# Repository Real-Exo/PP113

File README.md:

Portable version of the Project 113 headphone amplifier, with added BlueTooth and 3D printable case.
Powered by 4 removable 18650 Li-ion cells, have to be charged externally.
Kicad 7.0 schematics & PCB layouts.
MPLAB X IDE firmware project.
FreeCAD case design files & gcode.

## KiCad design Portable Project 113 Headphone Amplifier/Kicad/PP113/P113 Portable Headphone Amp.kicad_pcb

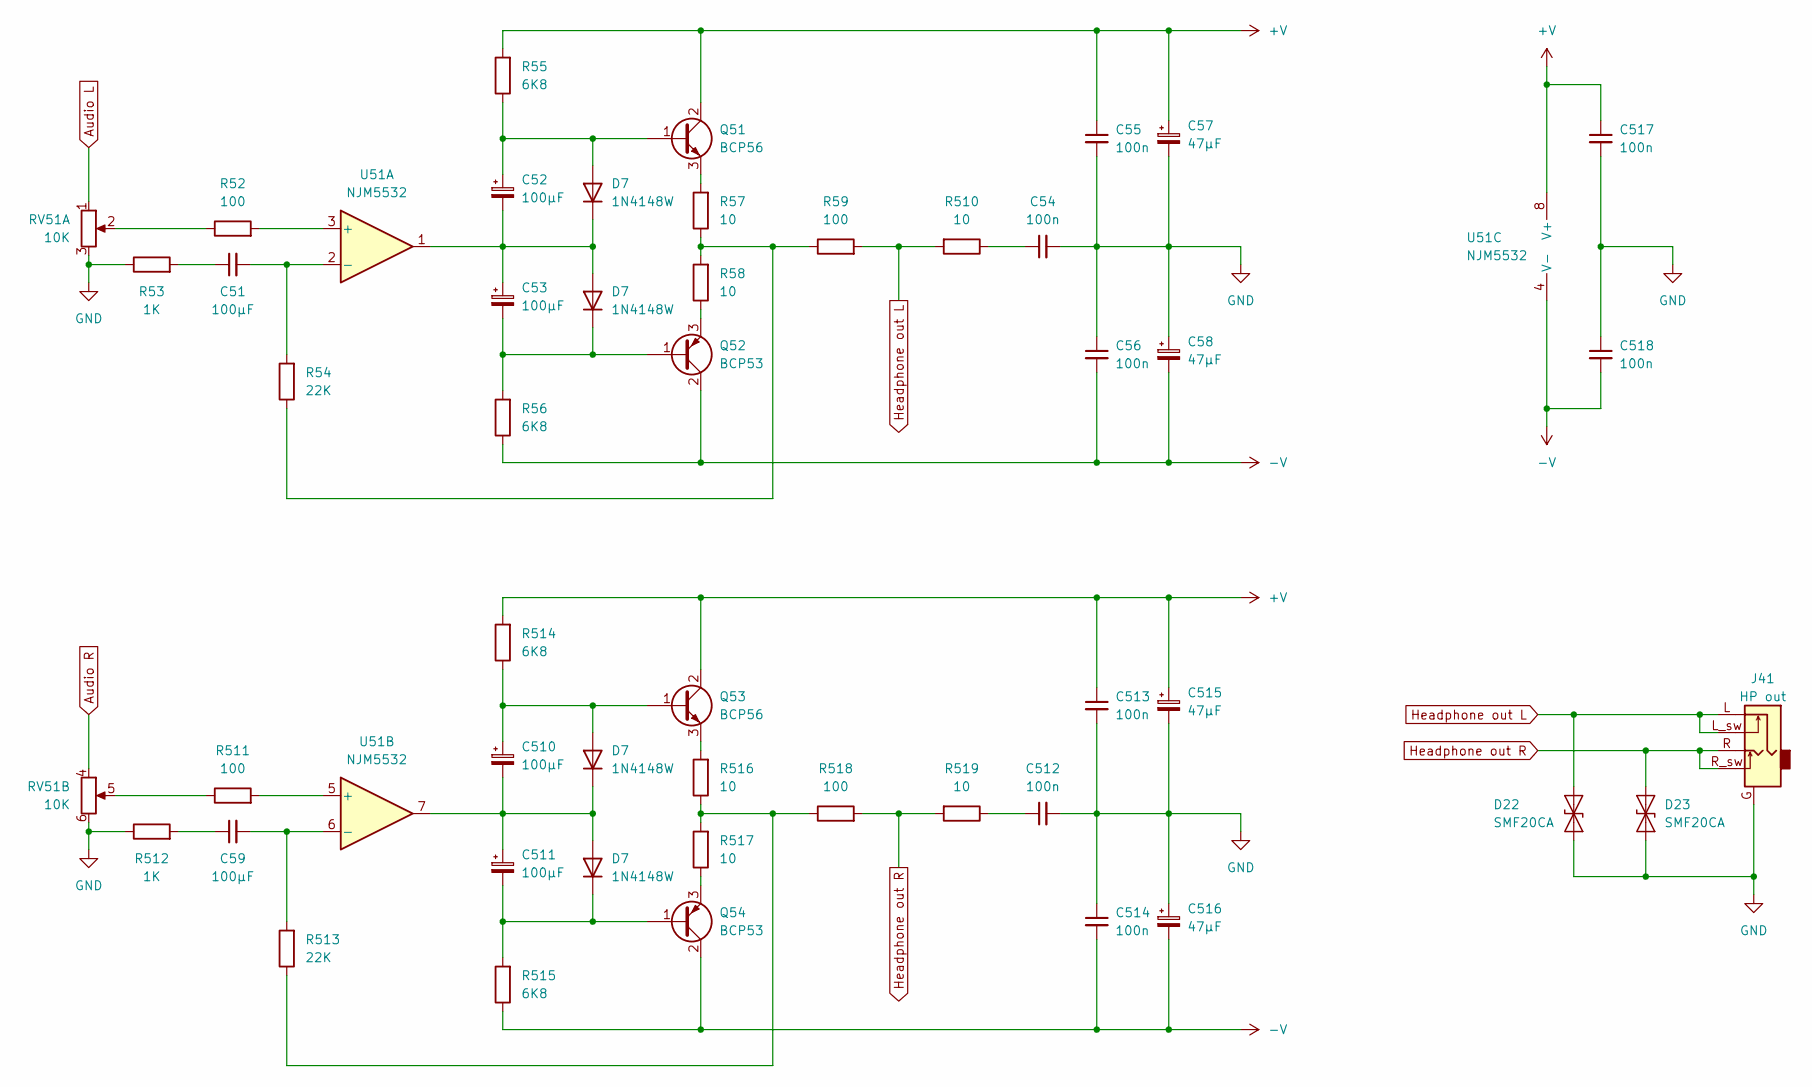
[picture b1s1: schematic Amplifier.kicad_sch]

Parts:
C51, C59: 100µF; CP_Elec_8x5.4
C52, C53, C510, C511: 100µF; CP_Elec_6.3x5.4_Nichicon
C54, C55, C56, C512, C513, C514, C517, C518: 100n; C_0805_2012Metric_Pad1.18x1.45mm_HandSolder
C57, C58, C515, C516: 47µF; CP_Elec_6.3x5.7
D7: 1N4148W; D_SOD-123
D22, D23: SMF20CA; D_SOD-123
J41: HP out; 3-5mm_connector
Q51, Q53: BCP56; SOT-223-3_TabPin2
Q52, Q54: BCP53; SOT-223-3_TabPin2
R52, R511: 100; R_0805_2012Metric_Pad1.20x1.40mm_HandSolder
R53, R512: 1K; R_0805_2012Metric_Pad1.20x1.40mm_HandSolder
R54, R513: 22K; R_0805_2012Metric_Pad1.20x1.40mm_HandSolder
R55, R56, R514, R515: 6K8; R_0805_2012Metric_Pad1.20x1.40mm_HandSolder
R57, R58, R510, R516, R517, R519: 10; R_1206_3216Metric_Pad1.30x1.75mm_HandSolder
R59, R518: 100; R_2512_6332Metric_Pad1.40x3.35mm_HandSolder
RV51: 10K; Potentiometer_Alps_RK09L_Double_Horizontal
U51: NJM5532; SOIC-8W_5.3x5.3mm_P1.27mm

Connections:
+V: C55.1, C57.1, C513.1, C515.1, C517.1, Q51.2 (C), Q53.2 (C), R55.2, R514.2, U51.8 (V+); also elsewhere on the board
-V: C56.2, C58.2, C514.2, C516.2, C518.2, Q52.2 (C), Q54.2 (C), R56.1, R515.1, U51.4 (V-); also elsewhere on the board
Audio L: RV51.1; also elsewhere on the board
Audio R: RV51.4; also elsewhere on the board
unnamed: C51.1, R53.2
unnamed: C54.1, R510.1
unnamed: C59.1, R512.2
unnamed: C512.1, R519.1
unnamed 55: C52.1, Q51.1 (B), R55.1; also elsewhere on the board
unnamed 56: C52.2, C53.1, U51.1; also elsewhere on the board
unnamed 57: C53.2, Q52.1 (B), R56.2; also elsewhere on the board
unnamed 58: C510.1, Q53.1 (B), R514.1; also elsewhere on the board
unnamed 59: C510.2, C511.1, U51.7; also elsewhere on the board
unnamed 60: C511.2, Q54.1 (B), R515.2; also elsewhere on the board
unnamed: Q51.3 (E), R57.2
unnamed: Q52.3 (E), R58.1
unnamed: Q53.3 (E), R516.2
unnamed: Q54.3 (E), R517.1
unnamed: R52.1, RV51.2
unnamed: R54.1, R57.1, R58.2, R59.1
unnamed: R511.1, RV51.5
unnamed: R513.1, R516.1, R517.2, R518.1
unnamed: R52.2, U51.3 (+)
unnamed: C51.2, R54.2, U51.2 (-)
unnamed: R511.2, U51.5 (+)
unnamed: C59.2, R513.2, U51.6 (-)

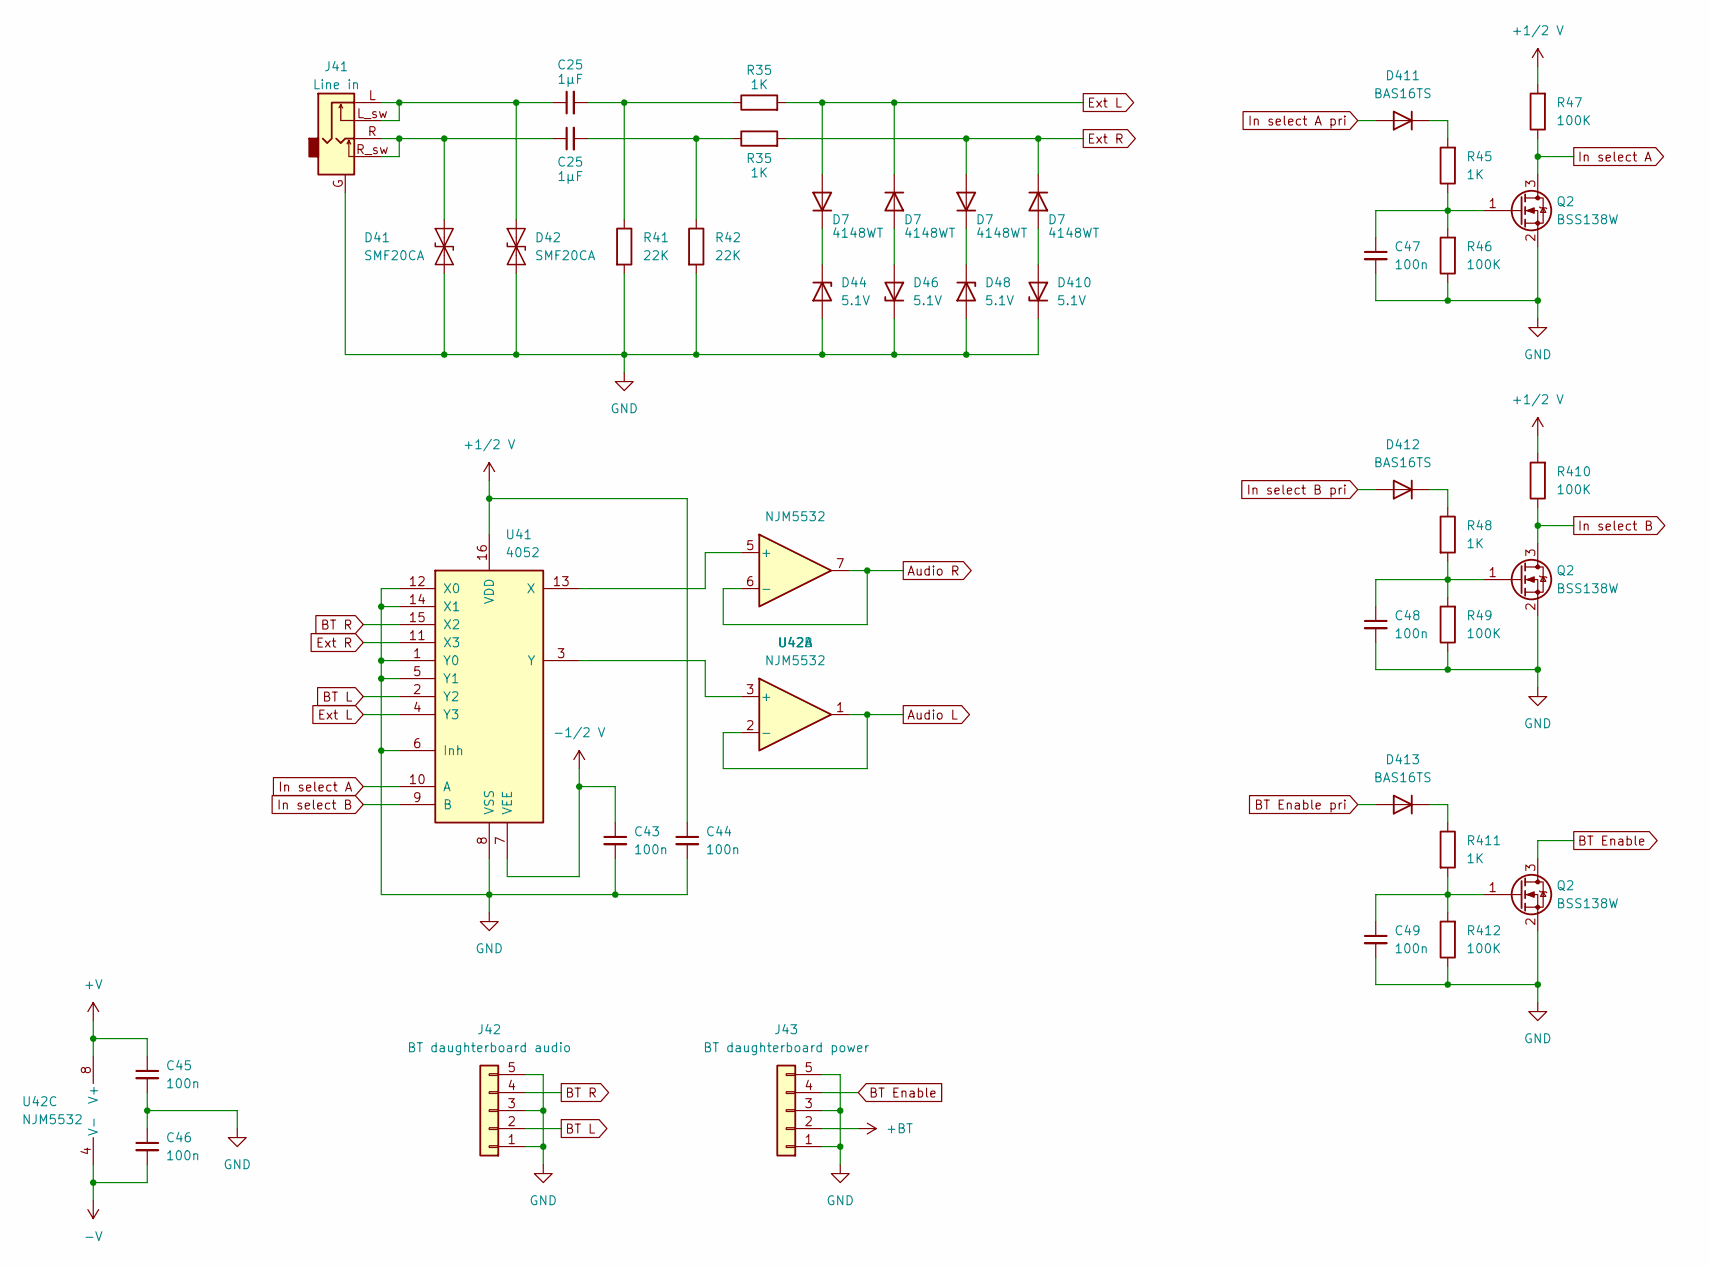
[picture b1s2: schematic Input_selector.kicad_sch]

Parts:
C25: 1µF; WIMA_1µF
C43, C44, C45, C46: 100n; C_0805_2012Metric_Pad1.18x1.45mm_HandSolder
C47, C48, C49: 100n; C_0402_1005Metric_Pad0.74x0.62mm_HandSolder JLC
D7: 4148WT; D_SOD-523
D41, D42: SMF20CA; D_SOD-123
D44, D46, D48, D410: 5.1V; D_SOD-323
D411, D412, D413: BAS16TS; D_SOD-523
J41: Line in; 3-5mm_connector
J42: BT daughterboard audio; PinSocket_1x05_P2.54mm_Vertical
J43: BT daughterboard power; PinSocket_1x05_P2.54mm_Vertical
Q2: BSS138W; SOT-323_SC-70
R35: 1K; R_2512_6332Metric_Pad1.40x3.35mm_HandSolder
R41, R42: 22K; R_1206_3216Metric_Pad1.30x1.75mm_HandSolder
R45, R48, R411: 1K; R_0402_1005Metric_Pad0.72x0.64mm_HandSolder JLC
R46, R47, R49, R410, R412: 100K; R_0402_1005Metric_Pad0.72x0.64mm_HandSolder JLC
U41: 4052; TSSOP-16_4.4x5mm_P0.65mm
U42: NJM5532; SOIC-8W_5.3x5.3mm_P1.27mm

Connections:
+1/2_V: C44.1, R47.2, R410.2, U41.16 (VDD); also elsewhere on the board
+BT: J43.2; also elsewhere on the board
+V: C45.1, U42.8 (V+); also elsewhere on the board
-1/2_V: C43.1, U41.7 (VEE); also elsewhere on the board
-V: C46.2, U42.4 (V-); also elsewhere on the board
Audio L: U42.1, U42.2 (-); also elsewhere on the board
Audio R: U42.6 (-), U42.7; also elsewhere on the board
BT Enable: J43.4; also elsewhere on the board
BT Enable pri: D413.2 (A); also elsewhere on the board
BT L: J42.2, U41.2 (Y2)
BT R: J42.4, U41.15 (X2)
Ext L: U41.4 (Y3); also elsewhere on the board
Ext R: U41.11 (X3); also elsewhere on the board
In select A: R47.1, U41.10 (A); also elsewhere on the board
In select A pri: D411.2 (A); also elsewhere on the board
In select B: R410.1, U41.9 (B); also elsewhere on the board
In select B pri: D412.2 (A); also elsewhere on the board
unnamed 52: D44.1 (K); also elsewhere on the board
unnamed 53: D46.2 (A); also elsewhere on the board
unnamed 54: D48.1 (K); also elsewhere on the board
unnamed 61: D410.2 (A); also elsewhere on the board
unnamed: D411.1 (K), R45.2
unnamed: D412.1 (K), R48.1
unnamed: D413.1 (K), R411.1
unnamed 92: C47.1, R45.1, R46.2; also elsewhere on the board
unnamed 93: C48.1, R48.2, R49.2; also elsewhere on the board
unnamed 94: C49.1, R411.2, R412.2; also elsewhere on the board
unnamed: U41.13 (X), U42.5 (+)
unnamed: U41.3 (Y), U42.3 (+)

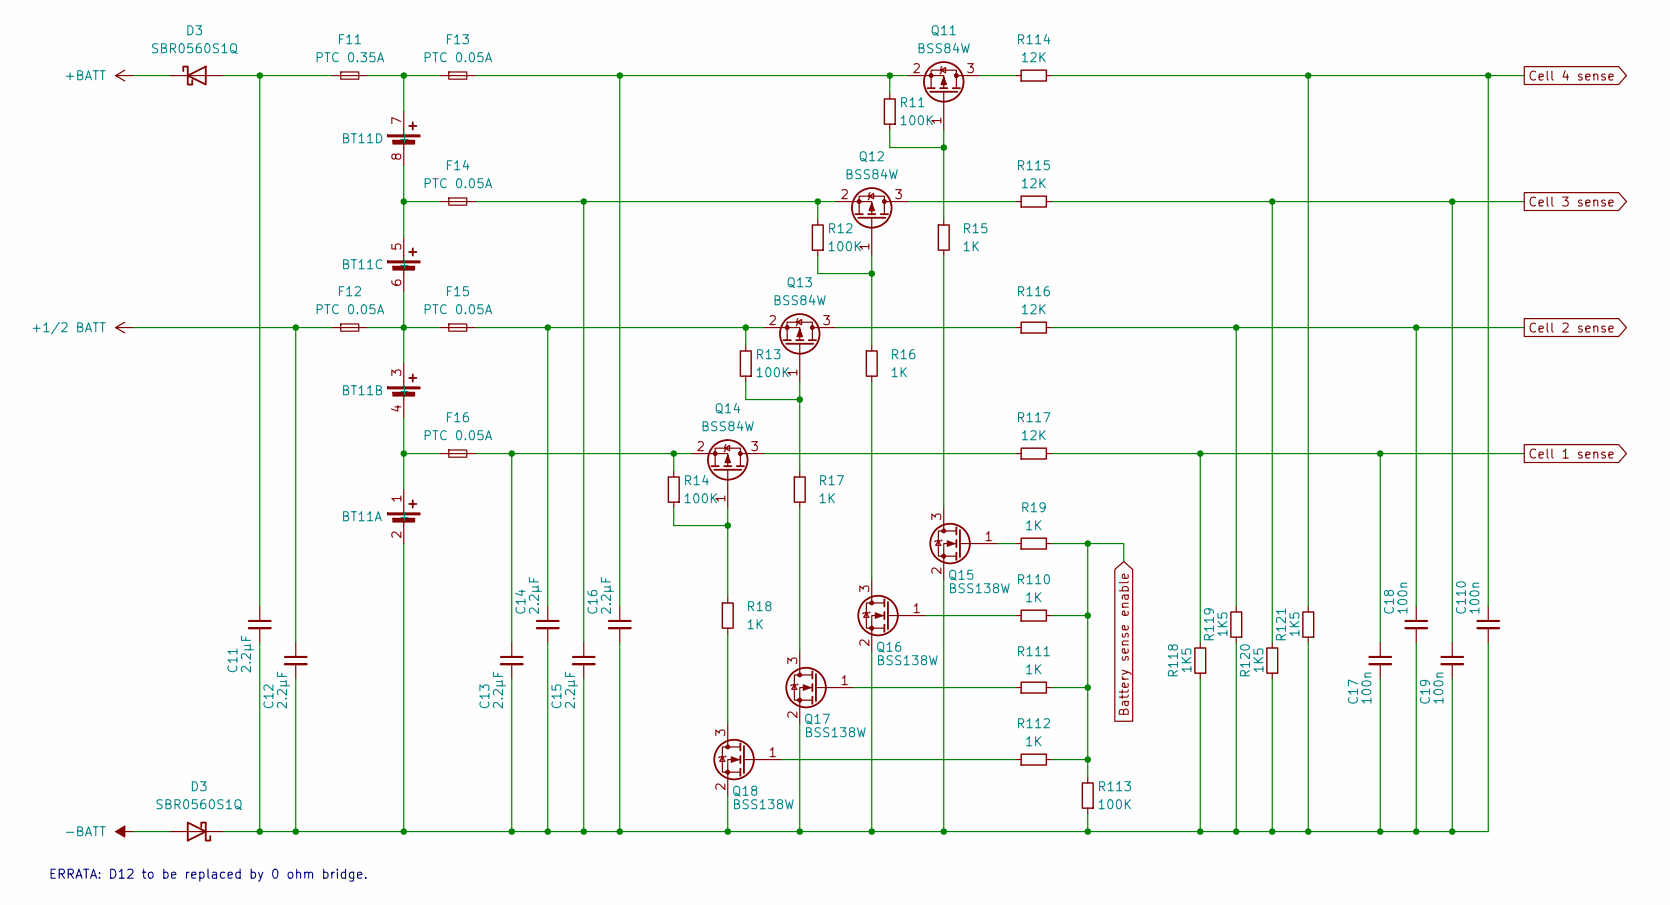
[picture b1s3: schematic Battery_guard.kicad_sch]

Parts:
BT11: Quad PCB mounted 18650 li-ion holder
C11, C12, C13, C14, C15, C16: 2.2µF; C_1206_3216Metric_Pad1.33x1.80mm_HandSolder
C17, C18, C19, C110: 100n; C_0402_1005Metric_Pad0.74x0.62mm_HandSolder JLC
D3: SBR0560S1Q; D_SOD-123
F11: PTC 0.35A; Fuse_1812_4532Metric_Pad1.30x3.40mm_HandSolder
F12, F13, F14, F15, F16: PTC 0.05A; Fuse_1206_3216Metric_Pad1.42x1.75mm_HandSolder
Q11, Q12, Q13, Q14: BSS84W; SOT-323_SC-70
Q15, Q16, Q17, Q18: BSS138W; SOT-323_SC-70
R11, R12, R13, R14, R113: 100K; R_0402_1005Metric_Pad0.72x0.64mm_HandSolder JLC
R15, R16, R17, R18, R19, R110, R111, R112: 1K; R_0402_1005Metric_Pad0.72x0.64mm_HandSolder JLC
R114, R115, R116, R117: 12K; R_0402_1005Metric_Pad0.72x0.64mm_HandSolder JLC
R118, R119, R120, R121: 1K5; R_0402_1005Metric_Pad0.72x0.64mm_HandSolder JLC

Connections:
+1/2_BATT: C12.1, F12.1; also elsewhere on the board
Battery sense enable: R19.2, R110.2, R111.2, R112.2, R113.2; also elsewhere on the board
Cell 1 sense: C17.1, R117.2, R118.2; also elsewhere on the board
Cell 2 sense: C18.1, R116.2, R119.2; also elsewhere on the board
Cell 3 sense: C19.1, R115.2, R120.2; also elsewhere on the board
Cell 4 sense: C110.1, R114.2, R121.2; also elsewhere on the board
unnamed: BT11.1 (+), BT11.4 (-), F16.1
unnamed 36: BT11.2 (-), C11.2, C12.2, C13.2, C14.2, C15.2, C16.2, C17.2, C18.2, C19.2, C110.2, Q15.2 (S), Q16.2 (S), Q17.2 (S), Q18.2 (S), R113.1, R118.1, R119.1, R120.1, R121.1; also elsewhere on the board
unnamed: BT11.3 (+), BT11.6 (-), F12.2, F15.1
unnamed: BT11.5 (+), BT11.8 (-), F14.1
unnamed: BT11.7 (+), F11.2, F13.1
unnamed 45: C11.1, F11.1; also elsewhere on the board
unnamed: Q11.3 (D), R114.1
unnamed: Q11.1 (G), R11.1, R15.1
unnamed: C16.1, F13.2, Q11.2 (S), R11.2
unnamed: Q12.3 (D), R115.1
unnamed: Q12.1 (G), R12.1, R16.1
unnamed: C15.1, F14.2, Q12.2 (S), R12.2
unnamed: Q13.3 (D), R116.1
unnamed: Q13.1 (G), R13.1, R17.1
unnamed: C14.1, F15.2, Q13.2 (S), R13.2
unnamed: Q14.3 (D), R117.1
unnamed: Q14.1 (G), R14.1, R18.1
unnamed: C13.1, F16.2, Q14.2 (S), R14.2
unnamed: Q15.3 (D), R15.2
unnamed: Q15.1 (G), R19.1
unnamed: Q16.3 (D), R16.2
unnamed: Q16.1 (G), R110.1
unnamed: Q17.3 (D), R17.2
unnamed: Q17.1 (G), R111.1
unnamed: Q18.3 (D), R18.2
unnamed: Q18.1 (G), R112.1

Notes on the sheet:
ERRATA: D12 to be replaced by 0 ohm bridge.

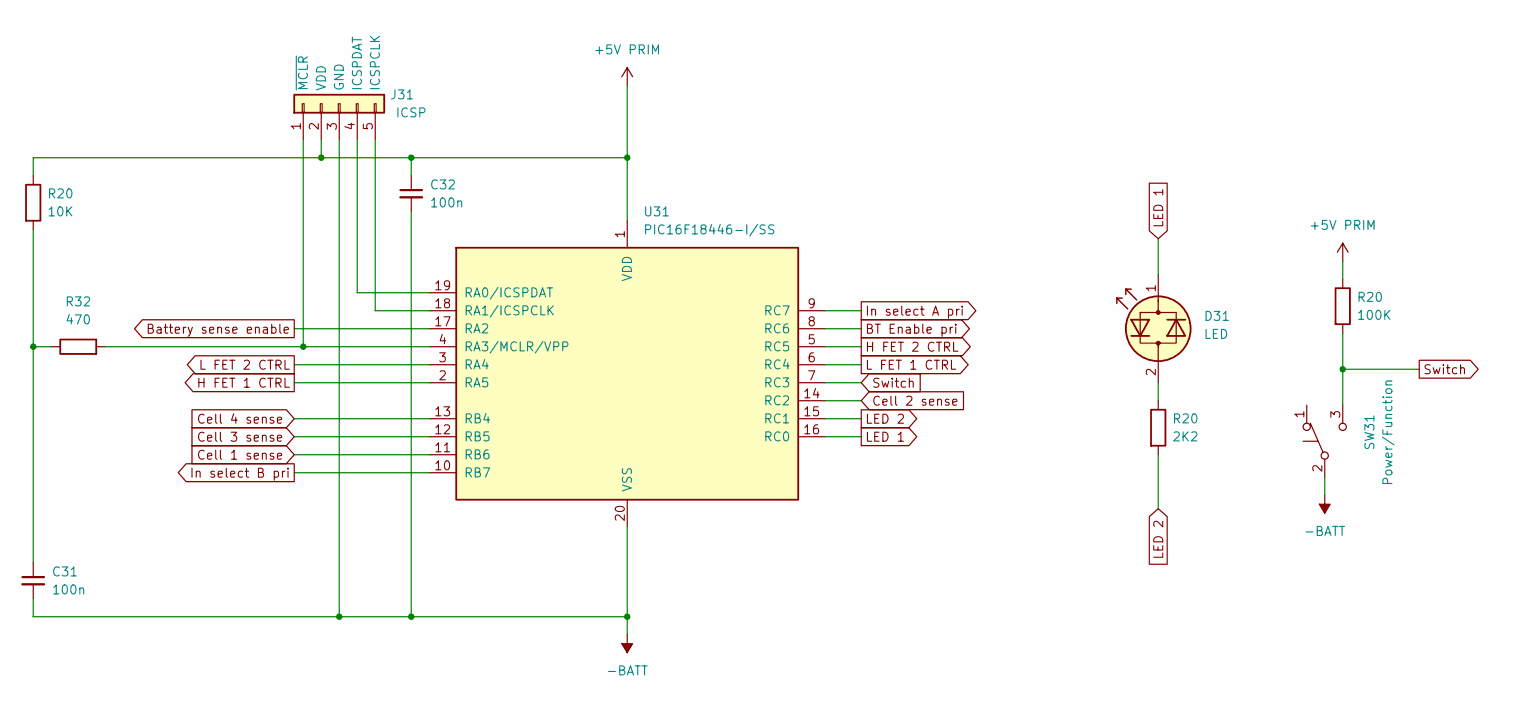
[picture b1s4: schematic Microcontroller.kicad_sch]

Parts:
C31, C32: 100n; C_0402_1005Metric_Pad0.74x0.62mm_HandSolder JLC
D31: LED; LED_Holder
J31: ICSP; PinSocket_1x05_P2.54mm_Vertical
R20: 2K2; R_0805_2012Metric_Pad1.20x1.40mm_HandSolder
R32: 470; R_0402_1005Metric_Pad0.72x0.64mm_HandSolder JLC
SW31: Power/Function; SW_LC1258EENP
U31: PIC16F18446-I/SS; SSOP-20_5.3x7.2mm_P0.65mm

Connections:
+5V_PRIM: C32.1, J31.2 (VDD), U31.1 (VDD); also elsewhere on the board
BT Enable pri: U31.8 (RC6); also elsewhere on the board
Battery sense enable: U31.17 (RA2); also elsewhere on the board
Cell 1 sense: U31.11 (RB6); also elsewhere on the board
Cell 2 sense: U31.14 (RC2); also elsewhere on the board
Cell 3 sense: U31.12 (RB5); also elsewhere on the board
Cell 4 sense: U31.13 (RB4); also elsewhere on the board
H FET 1 CTRL: U31.2 (RA5); also elsewhere on the board
H FET 2 CTRL: U31.5 (RC5); also elsewhere on the board
In select A pri: U31.9 (RC7); also elsewhere on the board
In select B pri: U31.10 (RB7); also elsewhere on the board
L FET 1 CTRL: U31.6 (RC4); also elsewhere on the board
L FET 2 CTRL: U31.3 (RA4); also elsewhere on the board
LED 1: D31.1 (KA), U31.16 (RC0)
LED 2: U31.15 (RC1); also elsewhere on the board
unnamed 40: C31.1, R32.1; also elsewhere on the board
unnamed 51: D31.2 (AK); also elsewhere on the board
unnamed: J31.5 (ICSPCLK), U31.18 (RA1/ICSPCLK)
unnamed: J31.4 (ICSPDAT), U31.19 (RA0/ICSPDAT)
unnamed: J31.1 (~MCLR), R32.2, U31.4 (RA3/MCLR/VPP)
Switch: SW31.3 (C), U31.7 (RC3); also elsewhere on the board

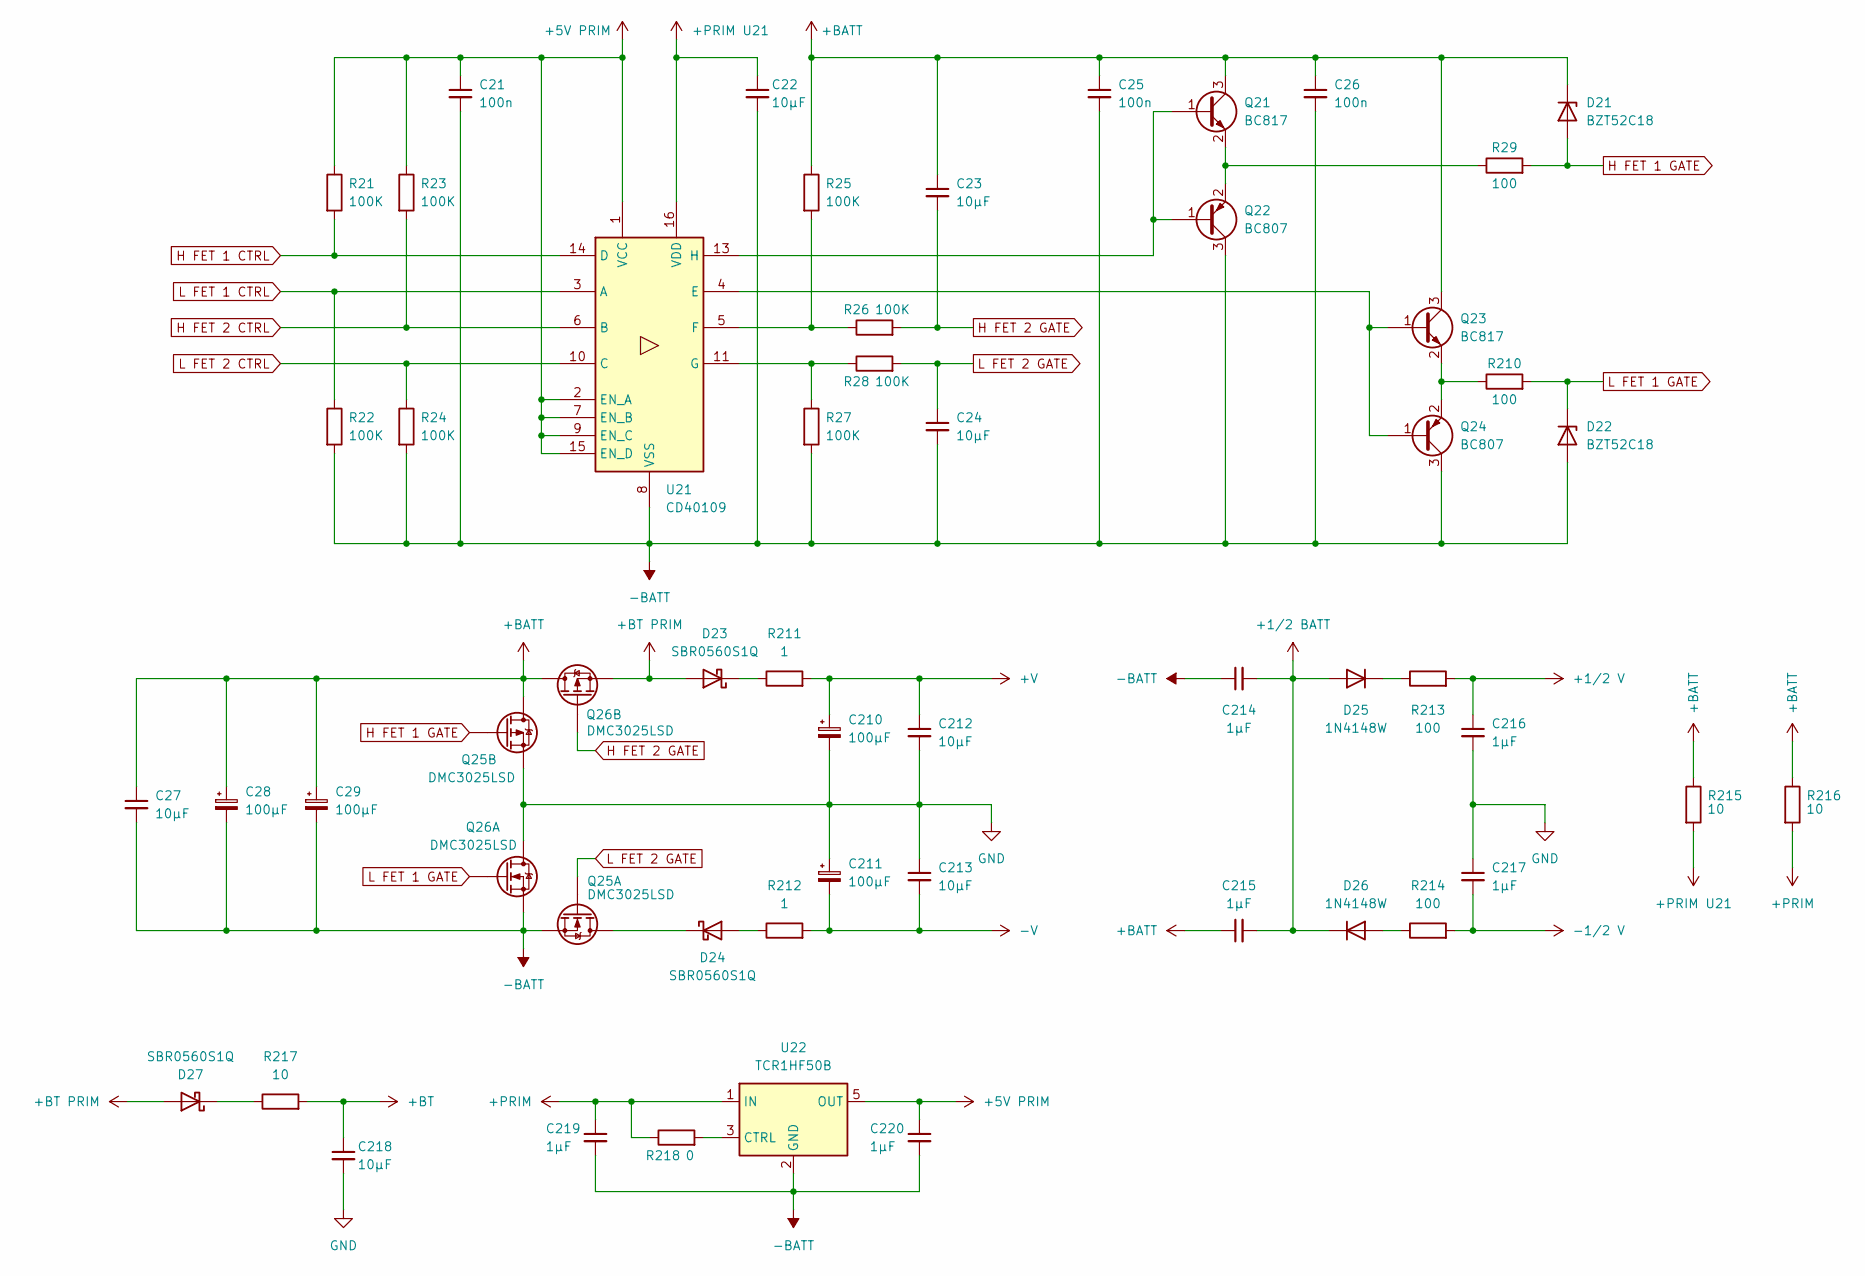
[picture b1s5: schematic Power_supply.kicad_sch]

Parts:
C21: 100n; C_0402_1005Metric_Pad0.74x0.62mm_HandSolder JLC
C22, C23, C24, C27, C212, C213, C218: 10µF; C_0805_2012Metric_Pad1.18x1.45mm_HandSolder
C25, C26: 100n; C_0805_2012Metric_Pad1.18x1.45mm_HandSolder
C28, C29, C210, C211: 100µF; CP_Radial_D6.3mm_P2.50mm
C214, C215, C216, C217, C219: 1µF; C_0805_2012Metric_Pad1.18x1.45mm_HandSolder
C220: 1µF; C_0402_1005Metric_Pad0.74x0.62mm_HandSolder JLC
D21, D22: BZT52C18; D_SOD-123
D23, D24, D27: SBR0560S1Q; D_SOD-123
D25, D26: 1N4148W; D_SOD-123
Q21, Q23: BC817; SOT-23
Q22, Q24: BC807; SOT-23
Q25, Q26: DMC3025LSD; SO-8_3.9x4.9mm_P1.27mm
R21, R22, R23, R24, R25, R26, R27, R28: 100K; R_0402_1005Metric_Pad0.72x0.64mm_HandSolder JLC
R29, R210, R213, R214: 100; R_0805_2012Metric_Pad1.20x1.40mm_HandSolder
R211, R212: 1; R_1206_3216Metric_Pad1.30x1.75mm_HandSolder
R215, R216, R217: 10; R_0805_2012Metric_Pad1.20x1.40mm_HandSolder
R218: 0; R_0402_1005Metric_Pad0.72x0.64mm_HandSolder JLC
U21: CD40109; TSSOP-16_4.4x5mm_P0.65mm
U22: TCR1HF50B; TSOT-23-5

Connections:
+1/2_BATT: C214.2, C215.2, D25.2 (A), D26.1 (K); also elsewhere on the board
+1/2_V: C216.1, R213.2; also elsewhere on the board
+5V_PRIM: C21.1, C220.1, R21.1, R23.1, U21.1 (VCC), U21.2 (EN_A), U21.7 (EN_B), U21.9 (EN_C), U21.15 (EN_D), U22.5 (OUT); also elsewhere on the board
+BT: C218.1, R217.2; also elsewhere on the board
+PRIM: C219.1, R216.2, R218.1, U22.1 (IN)
+PRIM_U21: C22.1, R215.2, U21.16 (VDD)
+V: C210.1, C212.1, R211.2; also elsewhere on the board
-1/2_V: C217.2, R214.2; also elsewhere on the board
-V: C211.2, C213.2, R212.2; also elsewhere on the board
H FET 1 CTRL: R21.2, U21.14 (D); also elsewhere on the board
H FET 1 GATE: D21.2 (A), Q25.4 (G1), R29.2
H FET 2 CTRL: R23.2, U21.6 (B); also elsewhere on the board
H FET 2 GATE: C23.2, Q26.4 (G1), R26.2
L FET 1 CTRL: R22.1, U21.3 (A); also elsewhere on the board
L FET 2 CTRL: R24.1, U21.10 (C); also elsewhere on the board
L FET 2 GATE: C24.1, Q25.2 (G2), R28.2
unnamed: D24.2 (A), R212.1
unnamed: D24.1 (K), Q25.7 (D2), Q25.8 (D2)
unnamed: D25.1 (K), R213.1
unnamed: D26.2 (A), R214.1
unnamed: D27.1 (K), R217.1
unnamed: Q21.1 (B), Q22.1 (B), U21.13 (H)
unnamed: Q21.2 (E), Q22.2 (E), R29.1
unnamed: Q23.1 (B), Q24.1 (B), U21.4 (E)
unnamed: Q23.2 (E), Q24.2 (E), R210.1
unnamed: R25.2, R26.1, U21.5 (F)
unnamed: R27.1, R28.1, U21.11 (G)
unnamed: R218.2, U22.3 (CTRL)

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
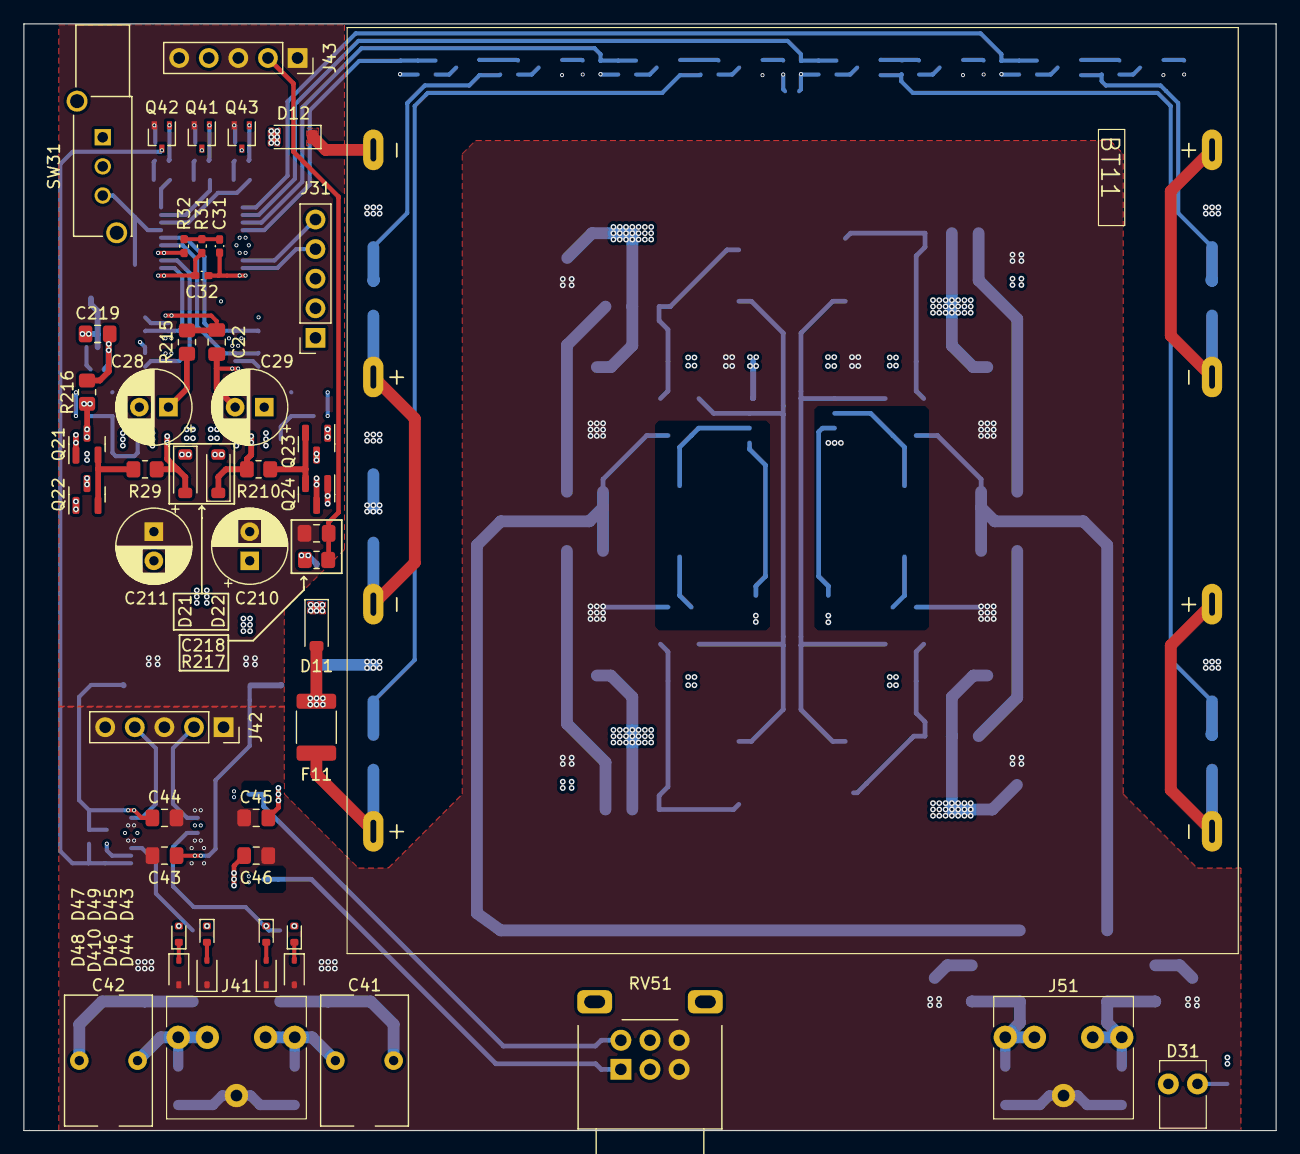
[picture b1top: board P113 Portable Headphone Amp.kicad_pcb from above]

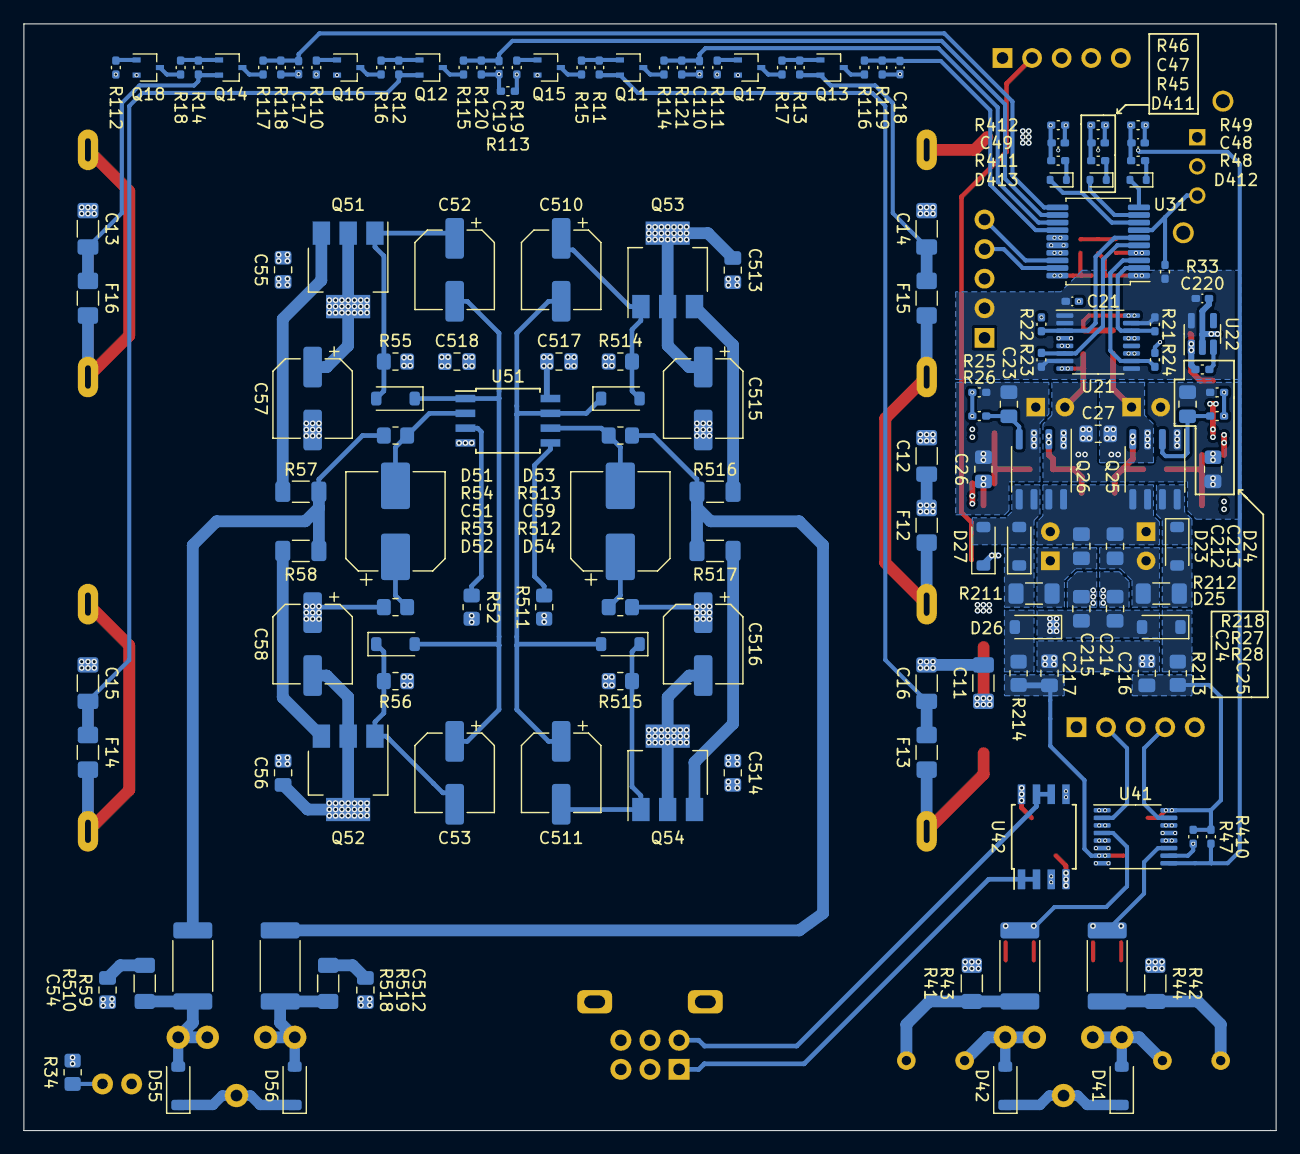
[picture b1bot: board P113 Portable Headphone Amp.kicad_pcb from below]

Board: 4 copper layers, 107.5 x 95.0 mm, 202 parts (151 on the bottom side), 125 nets.

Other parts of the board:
C41, C42: 1µF; WIMA_1µF
D11, D12: SBR0560S1Q; D_SOD-123
D43, D45, D47, D49: 4148WT; D_SOD-523
D51, D52, D53, D54: 1N4148W; D_SOD-123
D55, D56: SMF20CA; D_SOD-123
J51: Line in; 3-5mm_connector
Q41, Q42, Q43: BSS138W; SOT-323_SC-70
R31: 10K; R_0402_1005Metric_Pad0.72x0.64mm_HandSolder JLC
R33: 100K; R_0402_1005Metric_Pad0.72x0.64mm_HandSolder JLC
R34: 2K2; R_0805_2012Metric_Pad1.20x1.40mm_HandSolder
R43, R44: 1K; R_2512_6332Metric_Pad1.40x3.35mm_HandSolder

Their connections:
+5V_PRIM: R31.1, R33.1; also elsewhere on the board
BT Enable: Q43.3 (D); also elsewhere on the board
Ext L: D43.2 (A), D45.1 (K), R43.2; also elsewhere on the board
Ext R: D47.2 (A), D49.1 (K), R44.2; also elsewhere on the board
In select A: Q41.3 (D); also elsewhere on the board
In select B: Q42.3 (D); also elsewhere on the board
LED 2: R34.2; also elsewhere on the board
unnamed 36: D12.1 (K); also elsewhere on the board
unnamed 40: R31.2; also elsewhere on the board
unnamed 45: D11.2 (A); also elsewhere on the board
unnamed 51: R34.1; also elsewhere on the board
unnamed 52: D43.1 (K); also elsewhere on the board
unnamed 53: D45.2 (A); also elsewhere on the board
unnamed 54: D47.1 (K); also elsewhere on the board
unnamed 55: D51.2 (A); also elsewhere on the board
unnamed 56: D51.1 (K), D52.2 (A); also elsewhere on the board
unnamed 57: D52.1 (K); also elsewhere on the board
unnamed 58: D53.2 (A); also elsewhere on the board
unnamed 59: D53.1 (K), D54.2 (A); also elsewhere on the board
unnamed 60: D54.1 (K); also elsewhere on the board
unnamed 61: D49.2 (A); also elsewhere on the board
unnamed 92: Q41.1 (G); also elsewhere on the board
unnamed 93: Q42.1 (G); also elsewhere on the board
unnamed 94: Q43.1 (G); also elsewhere on the board
Switch: R33.2; also elsewhere on the board

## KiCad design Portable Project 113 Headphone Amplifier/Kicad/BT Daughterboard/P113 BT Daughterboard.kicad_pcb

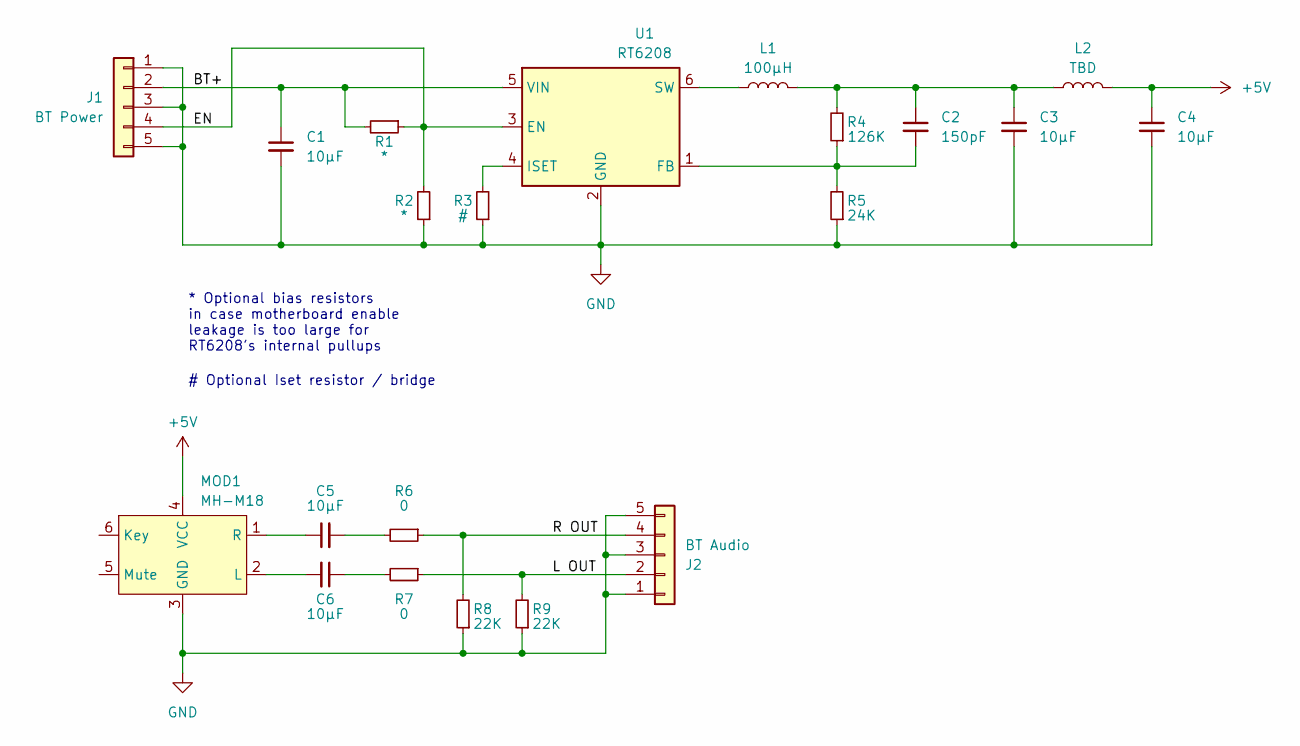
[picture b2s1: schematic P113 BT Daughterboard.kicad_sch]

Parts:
C1, C3, C4, C5, C6: 10µF; C_0805_2012Metric_Pad1.18x1.45mm_HandSolder
C2: 150pF; C_0805_2012Metric_Pad1.18x1.45mm_HandSolder
J1: BT Power; PinHeader_1x05_P2.54mm_Vertical
J2: BT Audio; PinHeader_1x05_P2.54mm_Vertical
L1: 100µH; L_Changjiang_FNR4026S
L2: TBD; L_Axial_L11.0mm_D4.5mm_P15.24mm_Horizontal_Fastron_MECC
MOD1: MH-M18
R1, R2: *; R_0805_2012Metric_Pad1.20x1.40mm_HandSolder
R3: #; R_0805_2012Metric_Pad1.20x1.40mm_HandSolder
R4: 126K; R_0805_2012Metric_Pad1.20x1.40mm_HandSolder
R5: 24K; R_0805_2012Metric_Pad1.20x1.40mm_HandSolder
R6, R7: 0; R_0805_2012Metric_Pad1.20x1.40mm_HandSolder
R8, R9: 22K; R_0805_2012Metric_Pad1.20x1.40mm_HandSolder
U1: RT6208; SOT-23-6

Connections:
+5V: C4.1, L2.2, MOD1.4 (VCC)
/BT+: C1.1, J1.2, R1.2, U1.5 (VIN)
/EN: J1.4, R1.1, R2.2, U1.3 (EN)
/L OUT: J2.2, R7.1, R9.2
/R OUT: J2.4, R6.1, R8.2
GND: C1.2, C3.2, C4.2, J1.1, J1.3, J1.5, J2.1, J2.3, J2.5, MOD1.3 (GND), R2.1, R3.1, R5.1, R8.1, R9.1, U1.2 (GND)
unnamed: C2.1, C3.1, L1.2, L2.1, R4.2
unnamed: C5.2, R6.2
unnamed: C6.1, R7.2
unnamed: C6.2, MOD1.2 (L)
unnamed: C5.1, MOD1.1 (R)
unnamed: C2.2, R4.1, R5.2, U1.1 (FB)
unnamed: R3.2, U1.4 (ISET)
unnamed: L1.1, U1.6 (SW)

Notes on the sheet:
* Optional bias resistors in case motherboard enable leakage is too large for RT6208's internal pullups
# Optional Iset resistor / bridge

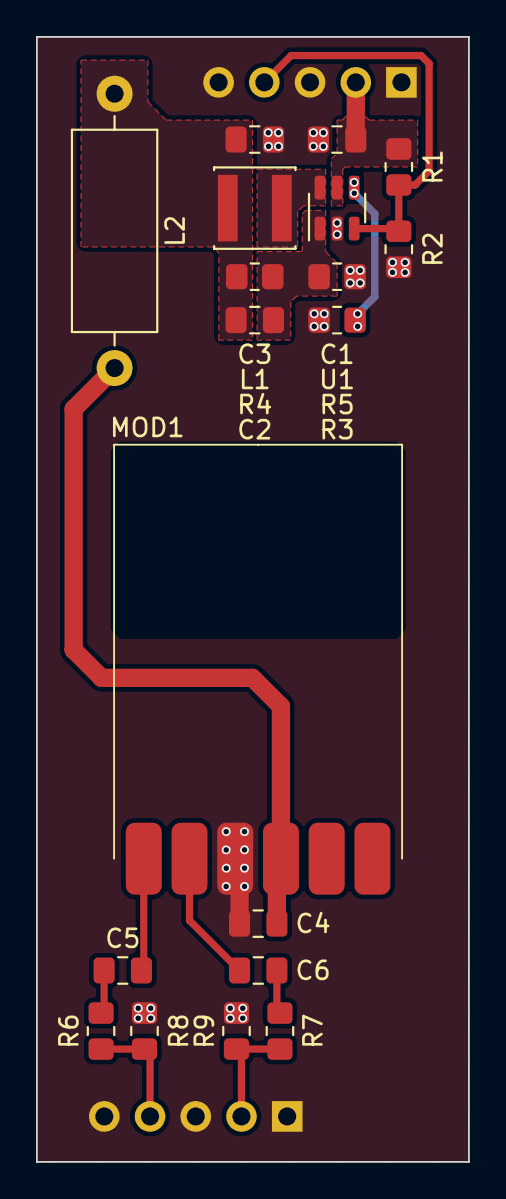
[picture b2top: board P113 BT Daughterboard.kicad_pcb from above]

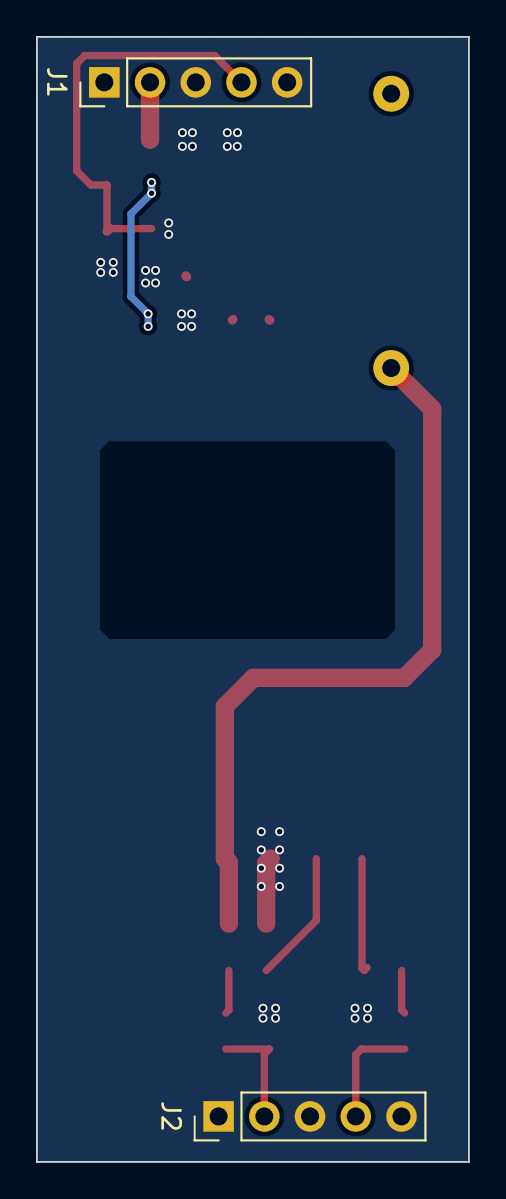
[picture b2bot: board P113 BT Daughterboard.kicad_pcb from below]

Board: 2 copper layers, 24.0 x 62.5 mm, 21 parts (2 on the bottom side), 14 nets.
